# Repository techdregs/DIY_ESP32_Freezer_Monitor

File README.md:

# DIY_Freezer_Monitor
 
DIY ESP32 PCB Series

Part 1: https://youtu.be/U1wLDvrBLVI

Part 2: https://youtu.be/l0SyRu5H_q8

Part 3: https://youtu.be/rO79X10tKIA

Part 4: https://youtu.be/QCU1oav9m0I

Part 5: https://youtu.be/EvdjFdHMEKg

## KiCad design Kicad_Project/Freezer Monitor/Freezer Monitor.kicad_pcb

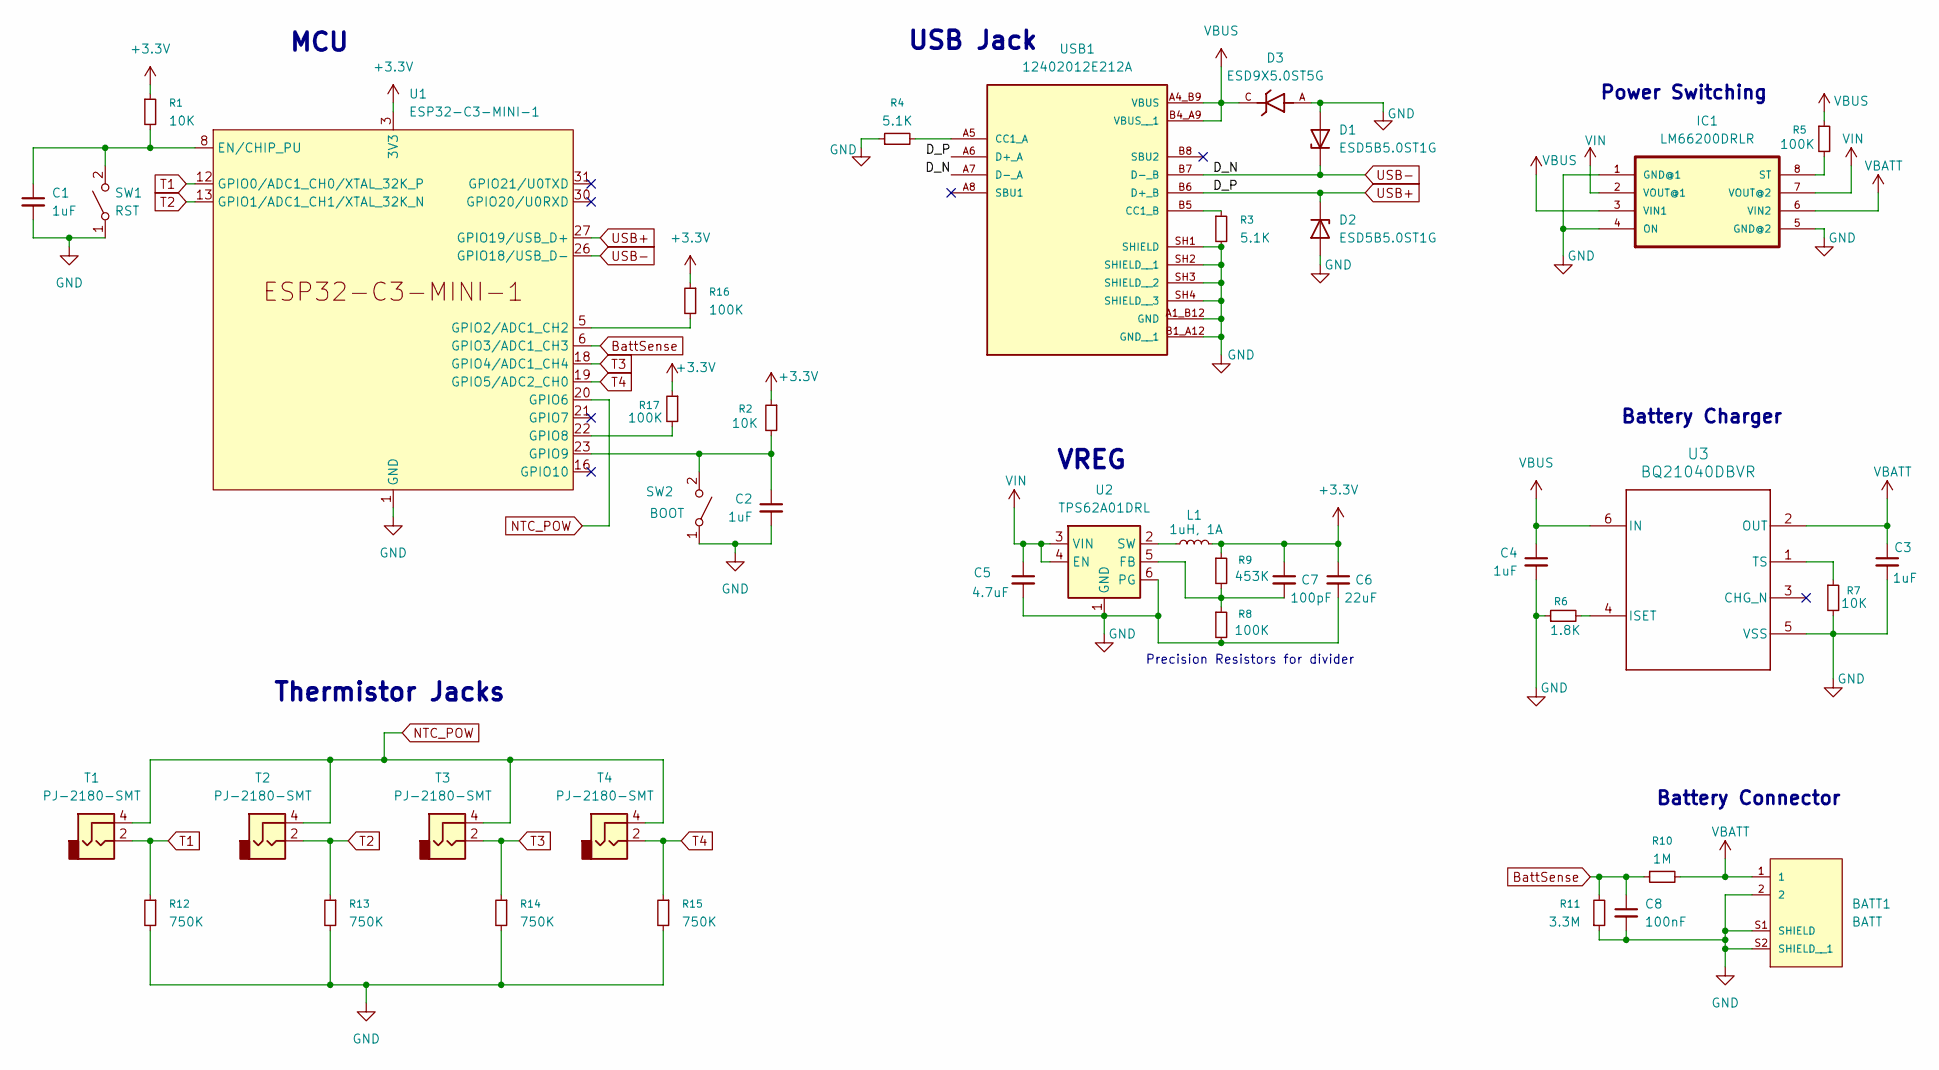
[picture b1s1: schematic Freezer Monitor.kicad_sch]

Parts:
BATT1: BATT; JST_S2B-PH-SM4-TB_LF__SN_
C1, C2, C3, C4: 1uF; C_0603_1608Metric
C5: 4.7uF; C_0603_1608Metric
C6: 22uF; C_0603_1608Metric
C7: 100pF; C_0603_1608Metric
C8: 100nF; C_0603_1608Metric
D1, D2: ESD5B5.0ST1G; D_SOD-523
D3: ESD9X5.0ST5G; SODFL1006X43N; PARTREV 8
IC1: LM66200DRLR; SOT8
L1: 1uH, 1A; L_1008_2520Metric
R1, R2, R7: 10K; R_0603_1608Metric
R3, R4: 5.1K; R_0603_1608Metric
R5, R8, R16, R17: 100K; R_0603_1608Metric
R6: 1.8K; R_0603_1608Metric
R9: 453K; R_0603_1608Metric
R10: 1M; R_0603_1608Metric
R11: 3.3M; R_0603_1608Metric
R12, R13, R14, R15: 750K; R_0603_1608Metric
SW1: RST; SW_TS-1088-AR02016
SW2: BOOT; SW_TS-1088-AR02016
T1, T2, T3, T4: PJ-2180-SMT; AUDIO-SMD_XKB_PJ-2180-SMT
U1: ESP32-C3-MINI-1
U2: TPS62A01DRL; SOT-563
U3: BQ21040DBVR; DBV0006A_N
USB1: 12402012E212A; AMPHENOL_12402012E212A; PARTREV 4

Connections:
+3.3V: C6.1, C7.1, L1.2, R1.1, R2.1, R9.1, R16.1, R17.1, U1.3 (3V3)
BattSense: C8.1, R10.1, R11.2, U1.6 (GPIO3/ADC1_CH3)
GND: BATT1.2, BATT1.S1 (SHIELD), BATT1.S2 (SHIELD__1), C1.2, C2.2, C3.2, C4.2, C5.2, C6.2, C8.2, D1.2 (A), D2.2 (A), D3.A, IC1.1 (GND@1), IC1.4 (ON), IC1.5 (GND@2), R3.2, R4.1, R6.1, R7.2, R8.2, R11.1, R12.2, R13.2, R14.2, R15.2, SW1.1 (A), SW2.1 (A), U1.1 (GND), U1.2 (GND), U1.11 (GND), U1.14 (GND), U1.36 (GND), U1.37 (GND), U1.38 (GND), U1.39 (GND), U1.40 (GND), U1.41 (GND), U1.42 (GND), U1.43 (GND), U1.44 (GND), U1.45 (GND), U1.46 (GND), U1.47 (GND), U1.48 (GND), U1.49 (GND), U1.50 (GND), U1.51 (GND), U1.52 (GND), U1.53 (GND), U2.1 (GND), U2.6 (PG), U3.5 (VSS), USB1.A1_B12 (GND), USB1.B1_A12 (GND__1), USB1.SH1 (SHIELD), USB1.SH2 (SHIELD__1), USB1.SH3 (SHIELD__2), USB1.SH4 (SHIELD__3)
NTC_POW: T1.4, T2.4, T3.4, T4.4, U1.20 (GPIO6)
unnamed: IC1.8 (ST), R5.2
unnamed: C1.1, R1.2, SW1.2 (B), U1.8 (EN/CHIP_PU)
unnamed: C2.1, R2.2, SW2.2 (B), U1.23 (GPIO9)
unnamed: R16.2, U1.5 (GPIO2/ADC1_CH2)
unnamed: R17.2, U1.22 (GPIO8)
unnamed: C7.2, R8.1, R9.2, U2.5 (FB)
unnamed: L1.1, U2.2 (SW)
unnamed: R6.2, U3.4 (ISET)
unnamed: R7.1, U3.1 (TS)
unnamed: R4.2, USB1.A5 (CC1_A)
unnamed: R3.1, USB1.B5 (CC1_B)
T1: R12.1, T1.2, U1.12 (GPIO0/ADC1_CH0/XTAL_32K_P)
T2: R13.1, T2.2, U1.13 (GPIO1/ADC1_CH1/XTAL_32K_N)
T3: R14.1, T3.2, U1.18 (GPIO4/ADC1_CH4)
T4: R15.1, T4.2, U1.19 (GPIO5/ADC2_CH0)
USB+: D2.1 (K), U1.27 (GPIO19/USB_D+), USB1.A6 (D+_A), USB1.B6 (D+_B)
USB-: D1.1 (K), U1.26 (GPIO18/USB_D-), USB1.A7 (D-_A), USB1.B7 (D-_B)
VBATT: BATT1.1, C3.1, IC1.6 (VIN2), R10.2, U3.2 (OUT)
VBUS: C4.1, D3.C, IC1.3 (VIN1), R5.1, U3.6 (IN), USB1.A4_B9 (VBUS), USB1.B4_A9 (VBUS__1)
VIN: C5.1, IC1.2 (VOUT@1), IC1.7 (VOUT@2), U2.3 (VIN), U2.4 (EN)

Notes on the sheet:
Thermistor Jacks
USB Jack
Battery Charger
VREG
MCU
Battery Connector
Precision Resistors for divider
Power Switching

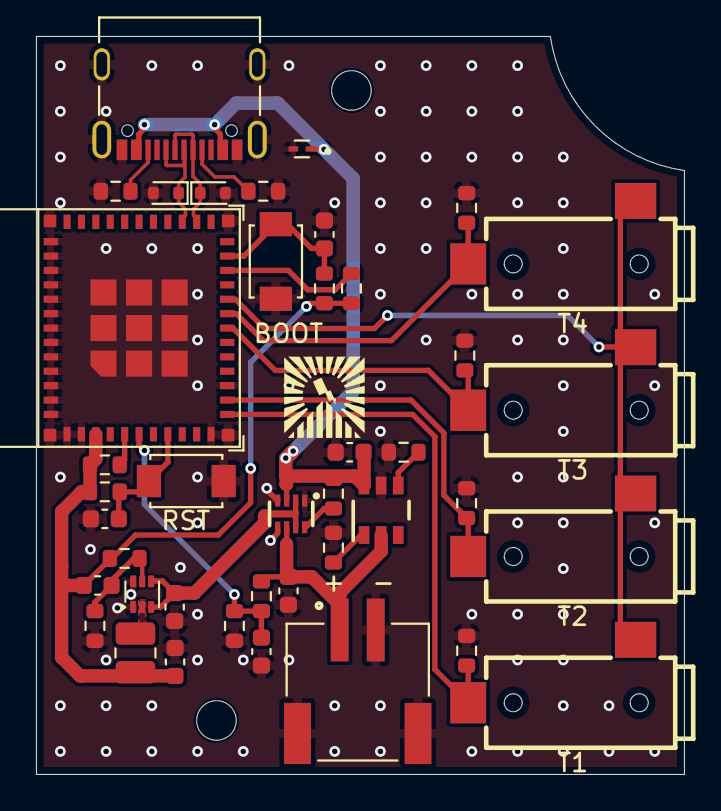
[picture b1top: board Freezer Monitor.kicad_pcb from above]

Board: 2 copper layers, 36.0 x 41.0 mm, 41 parts (0 on the bottom side), 24 nets.

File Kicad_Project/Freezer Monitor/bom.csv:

"Designator","Footprint","Quantity","Value","LCSC Part #"
"BATT1","JST_S2B-PH-SM4-TB_LF__SN_",1,"BATT","C2905019"
"C1, C2, C3, C4",603,4,"1uF","C15849"
"C5",603,1,"4.7uF","C19666"
"C6",603,1,"22uF","C60077"
"C7",603,1,"100pF","C14858"
"C8",603,1,"100nF","C14663"
"D1, D2","D_SOD-523",2,"ESD5B5.0ST1G","C29779759"
"D3","SODFL1006X43N",1,"ESD9X5.0ST5G","C87910"
"IC1","SOT8",1,"LM66200DRLR","C3235556"
"L1",1008,1,"1uH, 1A","C315711"
"R1, R2, R7",603,3,"10K","C25804"
"R10",603,1,"1M","C22935"
"R11",603,1,"3.3M","C26096"
"R12, R13, R14, R15",603,4,"750K","C861550"
"R16, R17, R5, R8",603,4,"100K","C25803"
"R3, R4",603,2,"5.1K","C23186"
"R6",603,1,"1.8K","C4177"
"R9",603,1,"453K","C861412"
"SW1","SW_TS-1088-AR02016",1,"RST","C720477"
"SW2","SW_TS-1088-AR02016",1,"BOOT","C720477"
"T1, T2, T3, T4","AUDIO-SMD_XKB_PJ-2180-SMT",4,"PJ-2180-SMT","C2885001"
"U1","ESP32-C3-MINI-1",1,"ESP32-C3-MINI-1","C2934569"
"U2","SOT-563",1,"TPS62A01DRL","C5157937"
"U3","DBV0006A_N",1,"BQ21040DBVR","C202311"
"USB1","AMPHENOL_12402012E212A",1,"12402012E212A","C2988369"
